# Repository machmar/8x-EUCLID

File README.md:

# 8x-EUCLID
an eight channel euclidian sequencer

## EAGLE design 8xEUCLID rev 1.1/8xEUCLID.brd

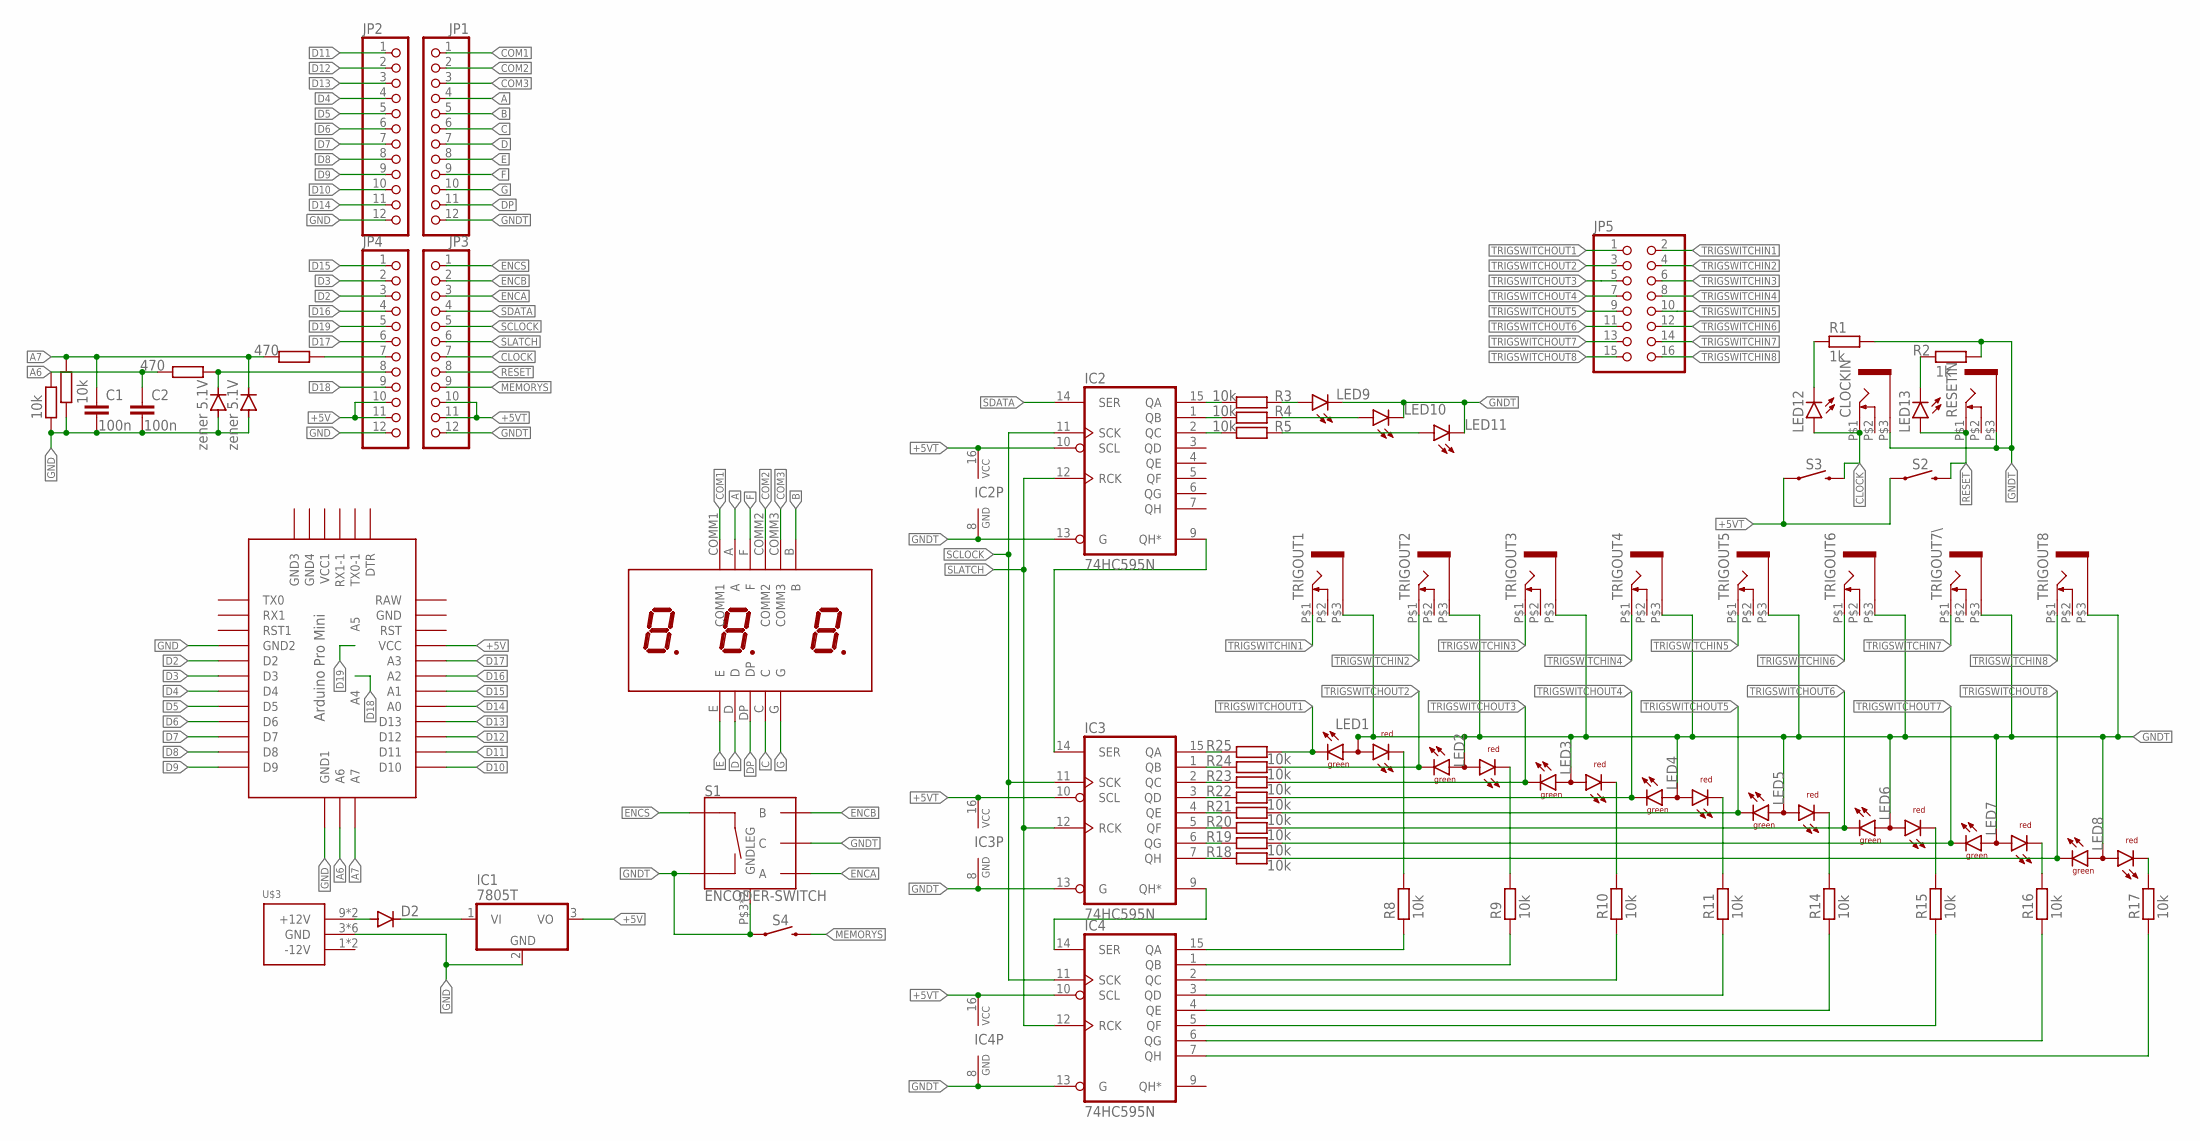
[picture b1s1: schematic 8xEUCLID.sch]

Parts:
C1, C2: 100n; C025-025X050
CLOCKIN: WQP-PJ301M-12_JACK
D1, D3: zener 5.1V; DO35-10
D2: 1N4004; DO41-10
IC1: 7805T; TO220H
IC2, IC3, IC4: 74HC595N; DIL16
JP1, JP2, JP3, JP4: PINHD-1X12-CB; 1X12-CB
JP5: PINHD-2X8; 2X08
LED1, LED2, LED3, LED4, LED5, LED6, LED7, LED8: L-115WEGW-CA; DUOLED-A-3MM
LED9, LED10, LED11: LED3MM
LED12, LED13: LED5MM
R1, R2: 1k; 0204V
R3, R4, R5, R8, R9, R10, R11, R14, R15, R16, R17, R18, R19, R20, R21, R22, R23, R24, R25: 10k; 0204V
R6, R7: 10k; 0204/7
R12, R13: 470; 0204/7
RESETIN: WQP-PJ301M-12_JACK
S1: ENCODER-SWITCH; ROTARY_ENC_PLAIN
S2, S3, S4: MOMENTARY-SWITCH-SPST-PTH-6.0MM; TACTILE_SWITCH_PTH_6.0MM
TRIGOUT1, TRIGOUT2, TRIGOUT3, TRIGOUT4, TRIGOUT5, TRIGOUT6, TRIGOUT7\, TRIGOUT8: WQP-PJ301M-12_JACK
U$1: 3DIGIT_SEVENSEGMENT; 3DIG_SEVSEG
U$2: ABK-PRO-MINI
U$3: POWER_SIMPLE10; POWER_10

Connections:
+5V: IC1.3 (VO), JP4.10, JP4.11, U$2.VCC
+5VT: IC2.10 (SCL), IC2.16 (VCC), IC3.10 (SCL), IC3.16 (VCC), IC4.10 (SCL), IC4.16 (VCC), JP3.10, JP3.11, S2.1, S3.1
A: JP1.4, U$1.A
A6: C2.1, R6.1, R12.2, U$2.A6
A7: C1.1, D3.C, R7.1, R13.2, U$2.A7
B: JP1.5, U$1.B
C: JP1.6, U$1.C
CLOCK: CLOCKIN.P$1 (2), JP3.7, LED12.A, S3.3 (2)
COM1: JP1.1, U$1.COMM1
COM2: JP1.2, U$1.COMM2
COM3: JP1.3, U$1.COMM3
D: JP1.7, U$1.D
D2: JP4.3, U$2.D2
D3: JP4.2, U$2.D3
D4: JP2.4, U$2.D4
D5: JP2.5, U$2.D5
D6: JP2.6, U$2.D6
D7: JP2.7, U$2.D7
D8: JP2.8, U$2.D8
D9: JP2.9, U$2.D9
D10: JP2.10, U$2.D10
D11: JP2.1, U$2.D11
D12: JP2.2, U$2.D12
D13: JP2.3, U$2.D13
D14: JP2.11, U$2.A0
D15: JP4.1, U$2.A1
D16: JP4.4, U$2.A2
D17: JP4.6, U$2.A3
D18: JP4.9, U$2.A4
D19: JP4.5, U$2.A5
DP: JP1.11, U$1.DP
E: JP1.8, U$1.E
ENCA: JP3.3, S1.A
ENCB: JP3.2, S1.B
ENCS: JP3.1, S1.SW+
F: JP1.9, U$1.F
G: JP1.10, U$1.G
GND: C1.2, C2.2, D1.A, D3.A, IC1.2 (GND), JP2.12, JP4.12, R6.2, R7.2, U$2.GND1 (GND2), U$2.GND4 (GND1), U$3.3 (GND), U$3.4 (GND), U$3.5 (GND), U$3.6 (GND), U$3.7 (GND), U$3.8 (GND)
GNDT: CLOCKIN.P$3 (1), IC2.8 (GND), IC2.13 (G), IC3.8 (GND), IC3.13 (G), IC4.8 (GND), IC4.13 (G), JP1.12, JP3.12, LED1.2 (A), LED2.2 (A), LED3.2 (A), LED4.2 (A), LED5.2 (A), LED6.2 (A), LED7.2 (A), LED8.2 (A), LED9.K (C), LED10.K (C), LED11.K (C), R1.2, R2.2, RESETIN.P$3 (1), S1.C, S1.P$3 (GNDLEG), S1.P$4 (GNDLEG), S1.SW-, S4.1, TRIGOUT1.P$3 (1), TRIGOUT2.P$3 (1), TRIGOUT3.P$3 (1), TRIGOUT4.P$3 (1), TRIGOUT5.P$3 (1), TRIGOUT6.P$3 (1), TRIGOUT7\.P$3 (1), TRIGOUT8.P$3 (1)
MEMORYS: JP3.9, S4.3 (2)
unnamed: IC2.9 (QH*), IC3.14 (SER)
unnamed: IC3.9 (QH*), IC4.14 (SER)
unnamed: JP4.7, R13.1
unnamed: D1.C, JP4.8, R12.1
unnamed: D2.A, U$3.9 (+12V), U$3.10 (+12V)
unnamed: LED8.3 (CR), R17.2
unnamed: IC3.7 (QH), R18.1
unnamed: LED7.3 (CR), R16.2
unnamed: D2.C, IC1.1 (VI)
unnamed: IC3.6 (QG), R19.1
unnamed: IC3.5 (QF), R20.1
unnamed: IC3.4 (QE), R21.1
unnamed: IC4.15 (QA), R8.1
unnamed: IC4.1 (QB), R9.1
unnamed: IC4.2 (QC), R10.1
unnamed: IC4.3 (QD), R11.1
unnamed: IC4.4 (QE), R14.1
unnamed: IC4.5 (QF), R15.1
unnamed: IC4.6 (QG), R16.1
unnamed: IC4.7 (QH), R17.1
unnamed: IC2.15 (QA), R3.1
unnamed: IC2.1 (QB), R4.1
unnamed: IC2.2 (QC), R5.1
unnamed: IC3.3 (QD), R22.1
unnamed: LED6.3 (CR), R15.2
unnamed: IC3.2 (QC), R23.1
unnamed: IC3.1 (QB), R24.1
unnamed: LED12.K (C), R1.1
unnamed: IC3.15 (QA), R25.1
unnamed: LED13.K (C), R2.1
unnamed: LED9.A, R3.2
unnamed: LED10.A, R4.2
unnamed: LED11.A, R5.2
unnamed: LED5.3 (CR), R14.2
unnamed: LED4.3 (CR), R11.2
unnamed: LED3.3 (CR), R10.2
unnamed: LED2.3 (CR), R9.2
unnamed: LED1.3 (CR), R8.2
RESET: JP3.8, LED13.A, RESETIN.P$1 (2), S2.3 (2)
SCLOCK: IC2.11 (SCK), IC3.11 (SCK), IC4.11 (SCK), JP3.5
SDATA: IC2.14 (SER), JP3.4
SLATCH: IC2.12 (RCK), IC3.12 (RCK), IC4.12 (RCK), JP3.6
TRIGSWITCHIN1: JP5.2, TRIGOUT1.P$1 (2)
TRIGSWITCHIN2: JP5.4, TRIGOUT2.P$1 (2)
TRIGSWITCHIN3: JP5.6, TRIGOUT3.P$1 (2)
TRIGSWITCHIN4: JP5.8, TRIGOUT4.P$1 (2)
TRIGSWITCHIN5: JP5.10, TRIGOUT5.P$1 (2)
TRIGSWITCHIN6: JP5.12, TRIGOUT6.P$1 (2)
TRIGSWITCHIN7: JP5.14, TRIGOUT7\.P$1 (2)
TRIGSWITCHIN8: JP5.16, TRIGOUT8.P$1 (2)
TRIGSWITCHOUT1: JP5.1, LED1.1 (CG), R25.2
TRIGSWITCHOUT2: JP5.3, LED2.1 (CG), R24.2
TRIGSWITCHOUT3: JP5.5, LED3.1 (CG), R23.2
TRIGSWITCHOUT4: JP5.7, LED4.1 (CG), R22.2
TRIGSWITCHOUT5: JP5.9, LED5.1 (CG), R21.2
TRIGSWITCHOUT6: JP5.11, LED6.1 (CG), R20.2
TRIGSWITCHOUT7: JP5.13, LED7.1 (CG), R19.2
TRIGSWITCHOUT8: JP5.15, LED8.1 (CG), R18.2

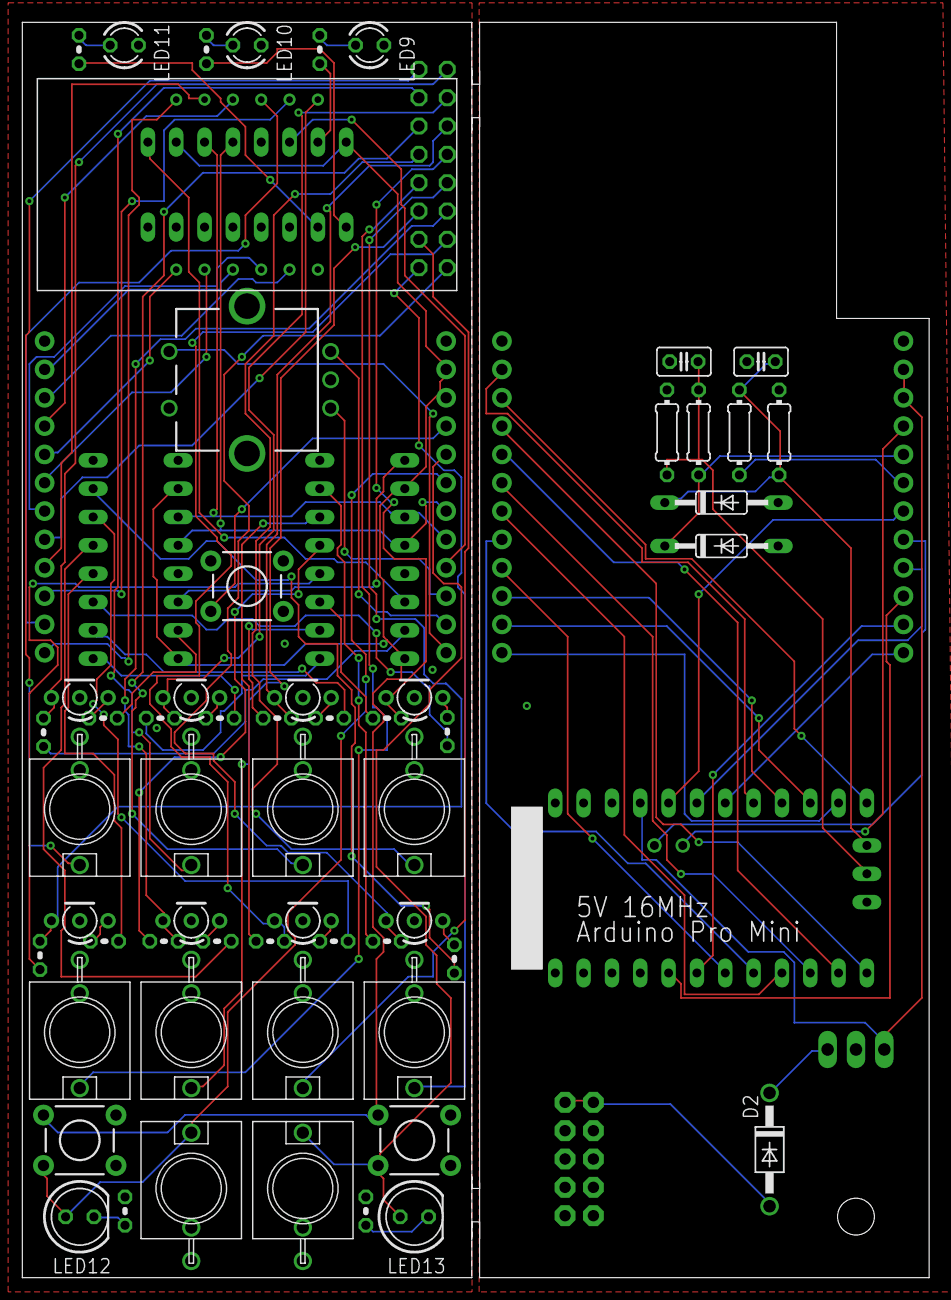
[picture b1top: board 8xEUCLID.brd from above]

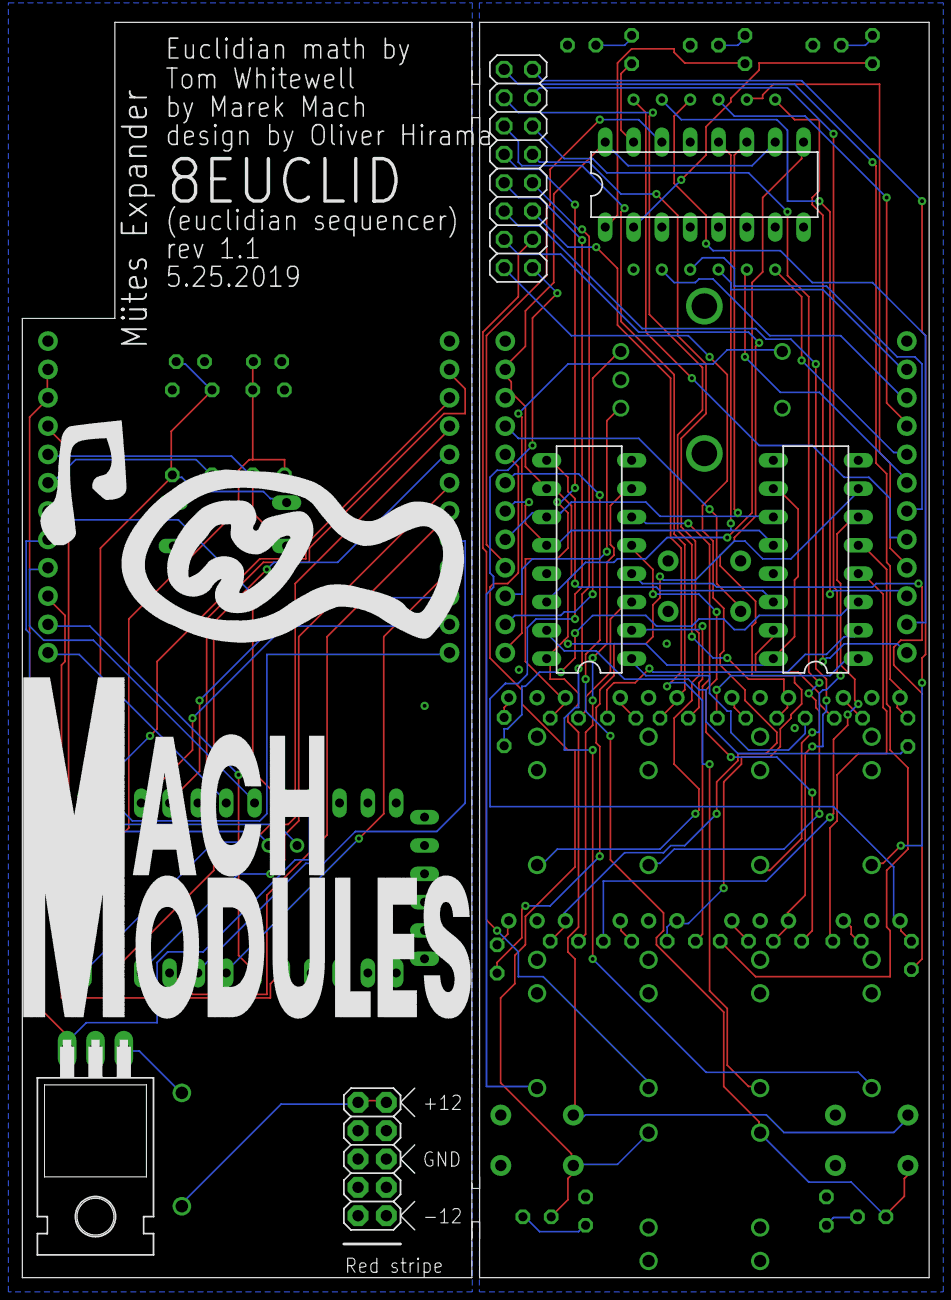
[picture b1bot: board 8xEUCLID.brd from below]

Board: 2 copper layers, 81.3 x 112.5 mm, 69 parts (6 on the bottom side), 98 nets.

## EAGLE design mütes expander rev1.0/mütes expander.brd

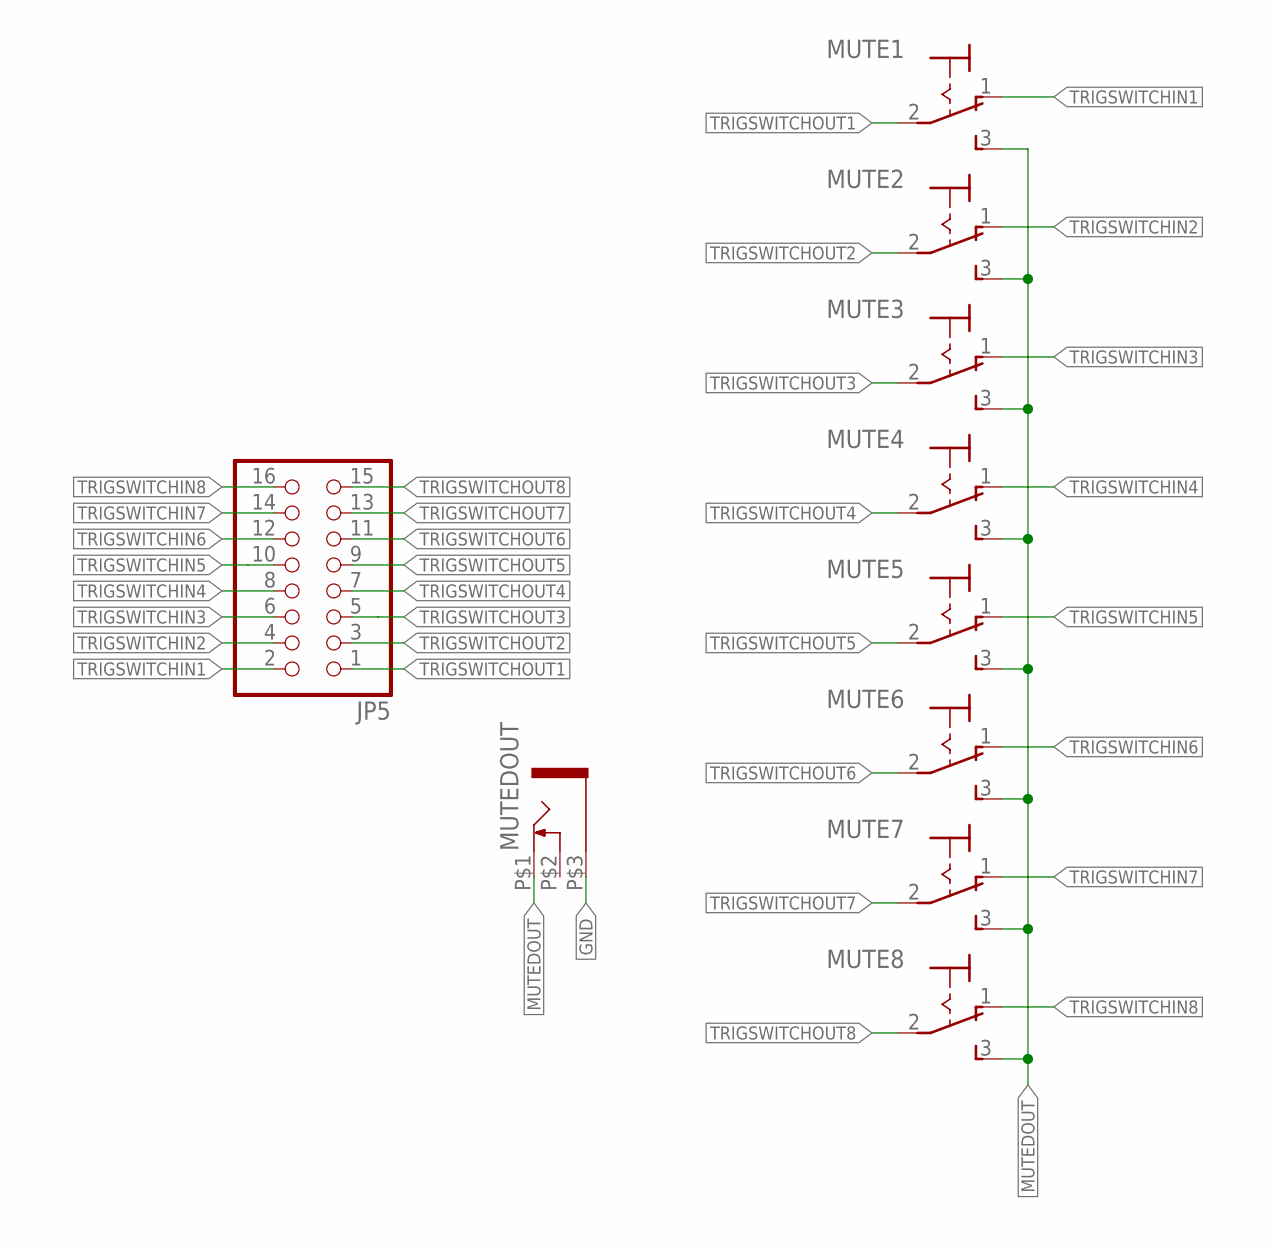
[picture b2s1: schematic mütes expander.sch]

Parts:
JP5: PINHD-2X8; 2X08
MUTE1, MUTE2, MUTE3, MUTE4, MUTE5, MUTE6, MUTE7, MUTE8: 320-916320-916BIG; 320-916MY
MUTEDOUT: WQP-PJ301M-12_JACK

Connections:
GND: MUTEDOUT.P$3 (1)
MUTEDOUT: MUTE1.3 (S), MUTE2.3 (S), MUTE3.3 (S), MUTE4.3 (S), MUTE5.3 (S), MUTE6.3 (S), MUTE7.3 (S), MUTE8.3 (S), MUTEDOUT.P$1 (2)
TRIGSWITCHIN1: JP5.2, MUTE1.1 (O)
TRIGSWITCHIN2: JP5.4, MUTE2.1 (O)
TRIGSWITCHIN3: JP5.6, MUTE3.1 (O)
TRIGSWITCHIN4: JP5.8, MUTE4.1 (O)
TRIGSWITCHIN5: JP5.10, MUTE5.1 (O)
TRIGSWITCHIN6: JP5.12, MUTE6.1 (O)
TRIGSWITCHIN7: JP5.14, MUTE7.1 (O)
TRIGSWITCHIN8: JP5.16, MUTE8.1 (O)
TRIGSWITCHOUT1: JP5.1, MUTE1.2
TRIGSWITCHOUT2: JP5.3, MUTE2.2
TRIGSWITCHOUT3: JP5.5, MUTE3.2
TRIGSWITCHOUT4: JP5.7, MUTE4.2
TRIGSWITCHOUT5: JP5.9, MUTE5.2
TRIGSWITCHOUT6: JP5.11, MUTE6.2
TRIGSWITCHOUT7: JP5.13, MUTE7.2
TRIGSWITCHOUT8: JP5.15, MUTE8.2

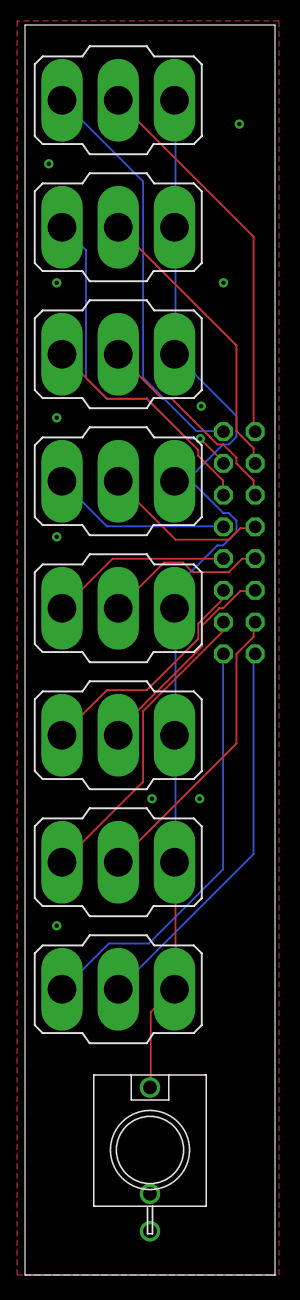
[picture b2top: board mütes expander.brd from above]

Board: 2 copper layers, 20.0 x 100.0 mm, 10 parts (1 on the bottom side), 17 nets.

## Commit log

2019-07-30 added hardware designs
2019-07-30 added code

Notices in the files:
parts and their libraries:
SparkFun-Switches: Licensing: Creative Commons ShareAlike 4.0 International - https://creativecommons.org/licenses/by-sa/4.0
